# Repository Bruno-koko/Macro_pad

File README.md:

# Macro_pad
My first project on forge webside. I hope it'll be okay

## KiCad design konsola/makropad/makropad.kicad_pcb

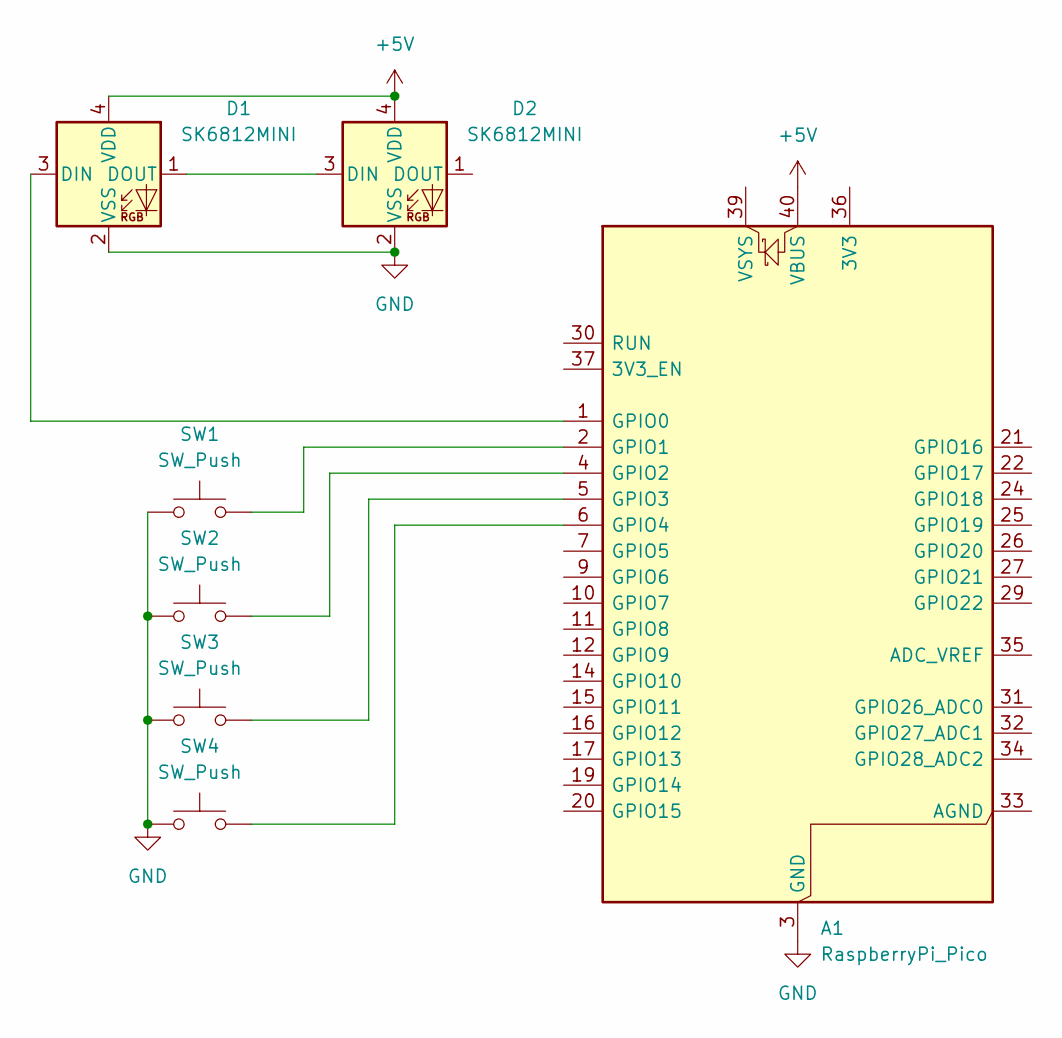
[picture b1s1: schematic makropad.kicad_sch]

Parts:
A1: RaspberryPi_Pico; RaspberryPi_Pico_Common_Unspecified
D1, D2: SK6812MINI; LED_SK6812MINI_PLCC4_3.5x3.5mm_P1.75mm
SW1, SW2, SW3, SW4: SW_Push; SW_Cherry_MX_1.00u_PCB

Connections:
+5V: A1.40 (VBUS), D1.4 (VDD), D2.4 (VDD)
GND: A1.3 (GND), A1.8 (GND), A1.13 (GND), A1.18 (GND), A1.23 (GND), A1.28 (GND), A1.38 (GND), D1.2 (VSS), D2.2 (VSS), SW1.1, SW2.1, SW3.1, SW4.1
unnamed: A1.1 (GPIO0), D1.3 (DIN)
unnamed: A1.2 (GPIO1), SW1.2
unnamed: A1.4 (GPIO2), SW2.2
unnamed: A1.5 (GPIO3), SW3.2
unnamed: A1.6 (GPIO4), SW4.2
unnamed: D1.1 (DOUT), D2.3 (DIN)

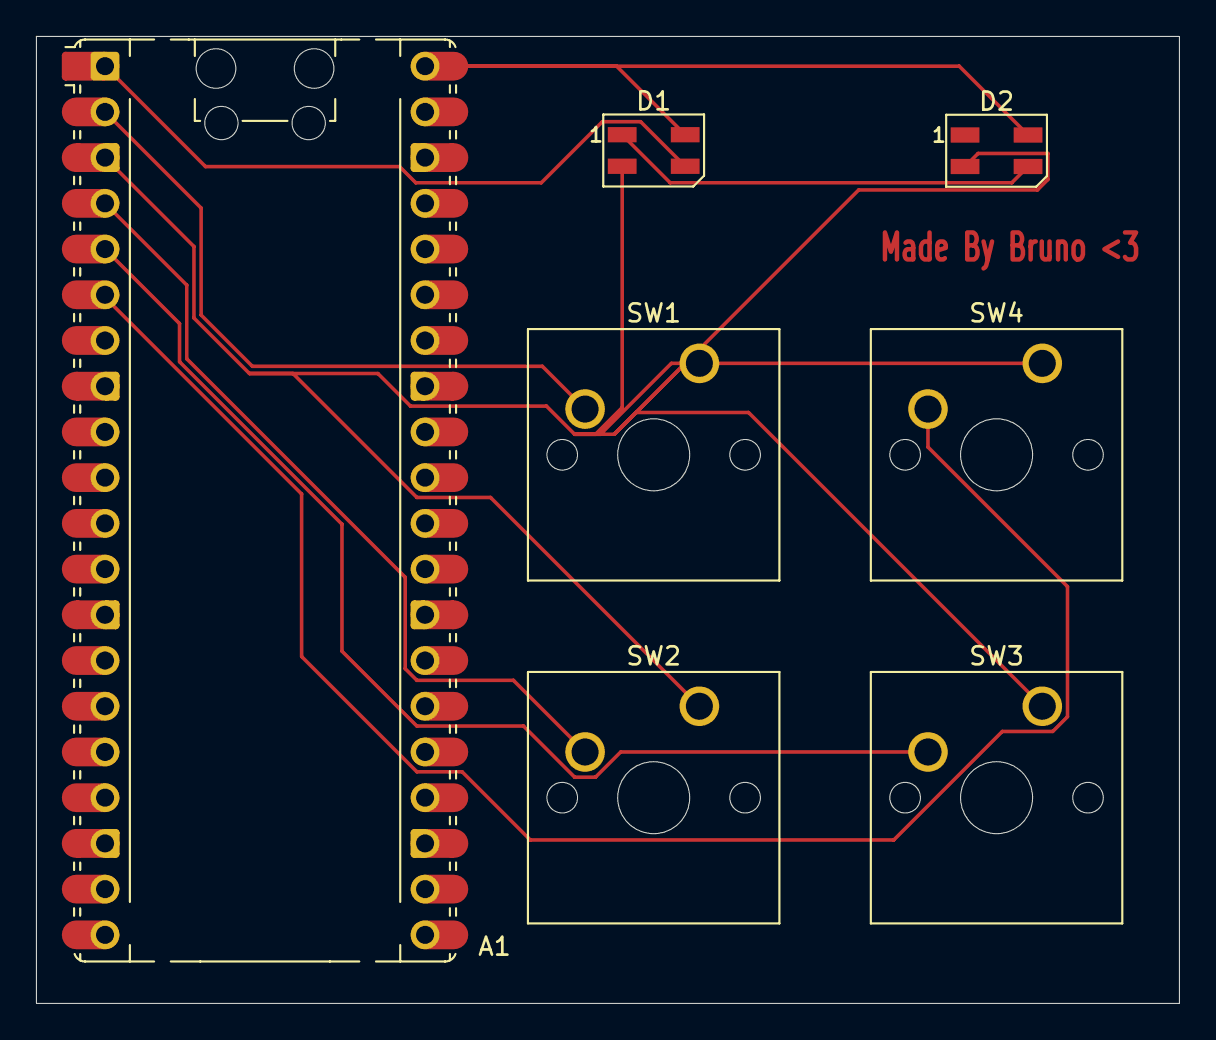
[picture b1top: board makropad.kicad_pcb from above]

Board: 2 copper layers, 63.5 x 53.7 mm, 7 parts (0 on the bottom side), 8 nets.
